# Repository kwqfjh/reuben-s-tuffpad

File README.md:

# Reuben's Tuffpad
A simple macropad with 3 keys, and A display.

" />
"" />

# Schematic

" />

# PCB 
The PCB was designed in KiCad and after v1,2,3,4,5,6 and 7, v8 is ready to roll!

" />

# Case
The case was designed in Fusion 360.

# Parts Used

1X Seeed XIAO RP2040,
4X MX-Style switches,
1X 0.91 inch OLED display,
4X DSA Keycaps,
4X M3x16mm screws,

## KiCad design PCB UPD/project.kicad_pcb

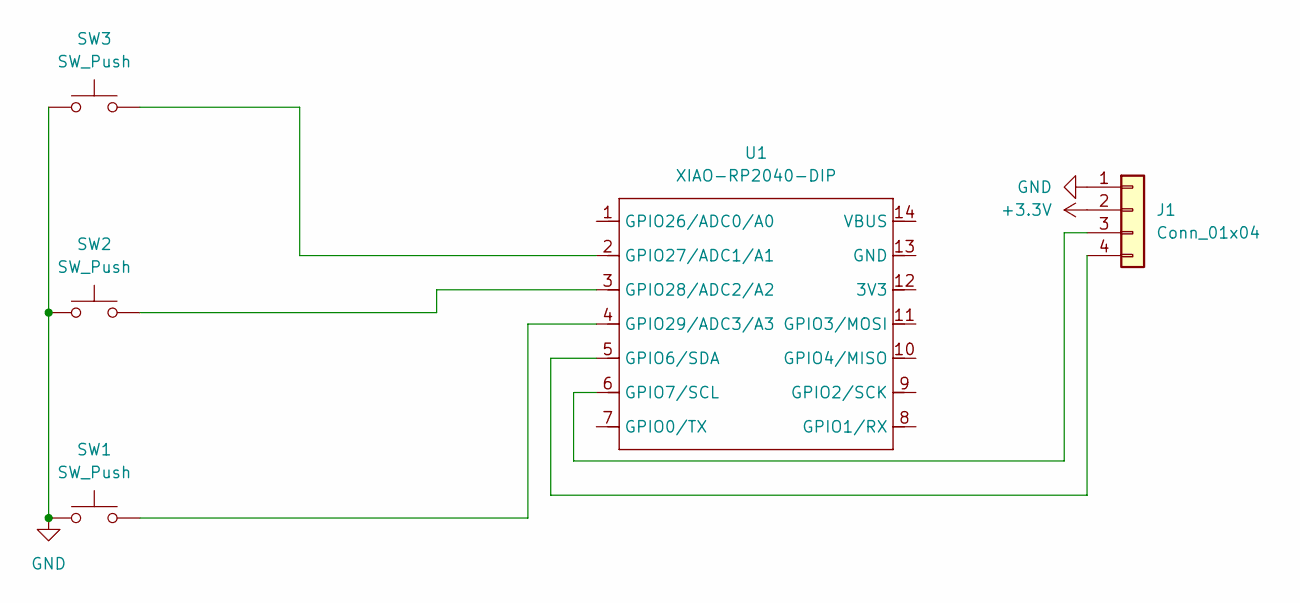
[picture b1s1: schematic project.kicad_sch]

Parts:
J1: Conn_01x04; SSD1306-0.91-OLED-4pin-128x32
SW1, SW2, SW3: SW_Push; SW_Cherry_MX_1.00u_PCB
U1: XIAO-RP2040-DIP; AAAAA

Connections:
+3.3V: J1.2
GND: J1.1, SW1.1, SW2.1, SW3.1
unnamed: J1.3, U1.6 (GPIO7/SCL)
unnamed: J1.4, U1.5 (GPIO6/SDA)
unnamed: SW3.2, U1.2 (GPIO27/ADC1/A1)
unnamed: SW2.2, U1.3 (GPIO28/ADC2/A2)
unnamed: SW1.2, U1.4 (GPIO29/ADC3/A3)

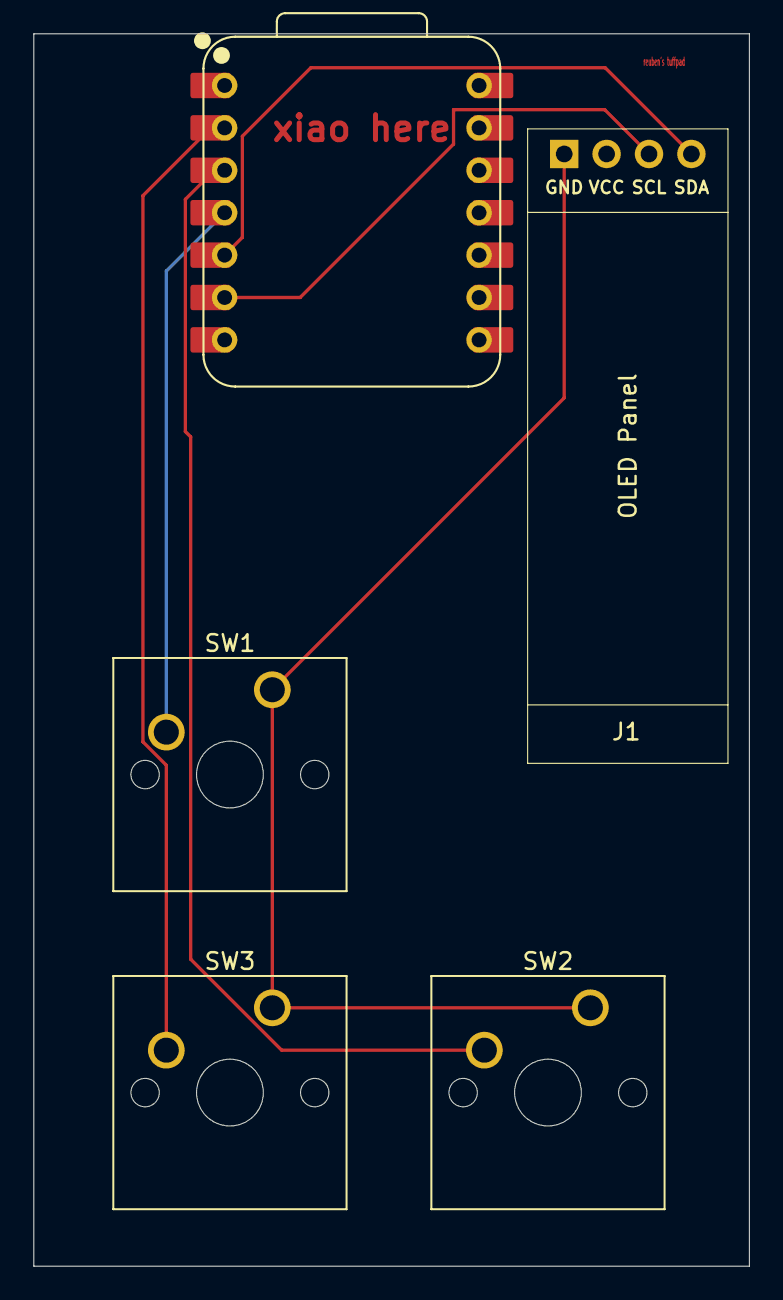
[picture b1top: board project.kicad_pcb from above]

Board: 2 copper layers, 42.9 x 73.8 mm, 5 parts (0 on the bottom side), 6 nets.

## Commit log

2025-12-06 Create temp
